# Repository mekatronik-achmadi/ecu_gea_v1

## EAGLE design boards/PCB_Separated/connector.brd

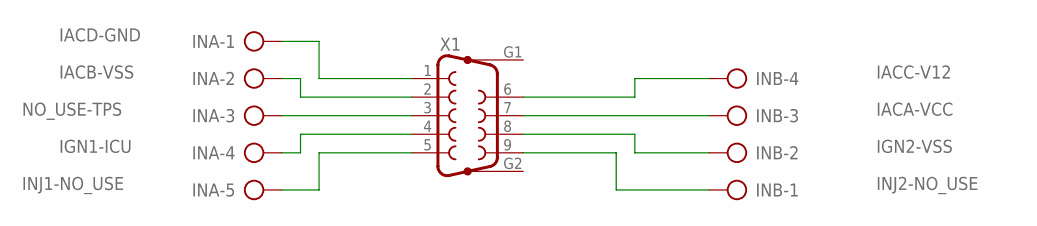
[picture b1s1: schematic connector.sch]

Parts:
INA: AK500/5
INB: AK500/4
X1: F09HP

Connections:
IACA-VCC: INB.3, X1.7
IACB-VSS: INA.2, X1.2
IACC-V12: INB.4, X1.6
IACD-GND: INA.1, X1.1
IGN1-ICU: INA.4, X1.4
IGN2-VSS: INB.2, X1.8
INJ1-NO_USE: INA.5, X1.5
INJ2-NO_USE: INB.1, X1.9
NO_USE-TPS: INA.3, X1.3

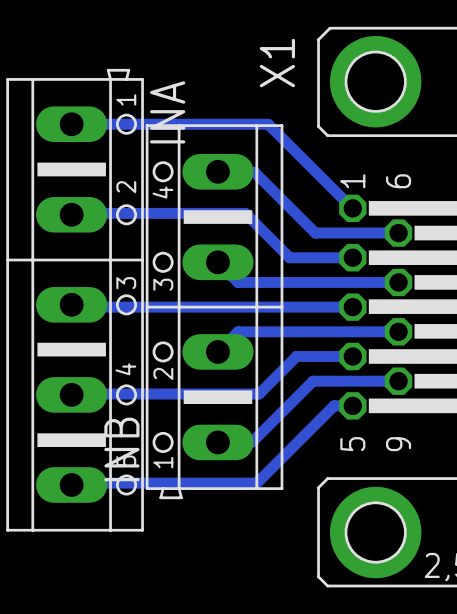
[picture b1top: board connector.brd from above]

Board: 2 copper layers, 3 parts (0 on the bottom side), 9 nets.

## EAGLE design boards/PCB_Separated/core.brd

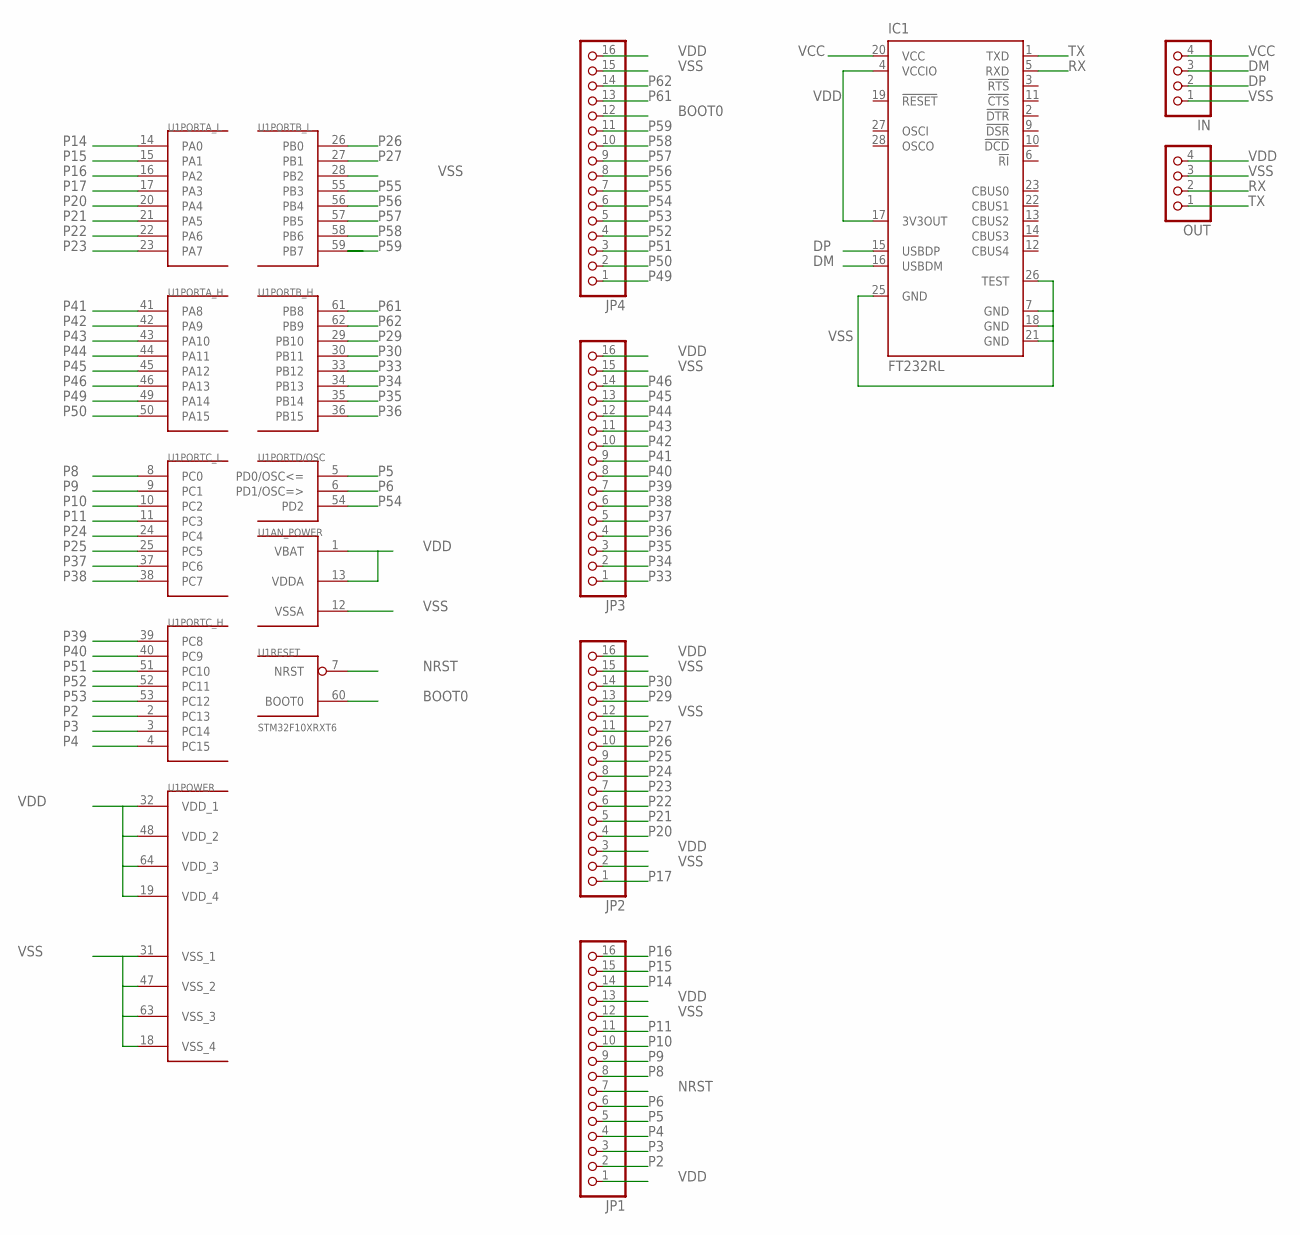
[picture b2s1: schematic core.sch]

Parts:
IC1: FT232RL; SSOP28
IN: PINHD-1X4; 1X04
JP1, JP2, JP3, JP4: PINHD-1X16; 1X16
OUT: PINHD-1X4; 1X04
U1: STM32F10XRXT6; TQFP64

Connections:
BOOT0: JP4.12, U1.60 (BOOT0)
DM: IC1.16 (USBDM), IN.3
DP: IC1.15 (USBDP), IN.2
NRST: JP1.7, U1.7 (NRST)
P2: JP1.2, U1.2 (PC13)
P3: JP1.3, U1.3 (PC14)
P4: JP1.4, U1.4 (PC15)
P5: JP1.5, U1.5 (PD0/OSC<=)
P6: JP1.6, U1.6 (PD1/OSC=>)
P8: JP1.8, U1.8 (PC0)
P9: JP1.9, U1.9 (PC1)
P10: JP1.10, U1.10 (PC2)
P11: JP1.11, U1.11 (PC3)
P14: JP1.14, U1.14 (PA0)
P15: JP1.15, U1.15 (PA1)
P16: JP1.16, U1.16 (PA2)
P17: JP2.1, U1.17 (PA3)
P20: JP2.4, U1.20 (PA4)
P21: JP2.5, U1.21 (PA5)
P22: JP2.6, U1.22 (PA6)
P23: JP2.7, U1.23 (PA7)
P24: JP2.8, U1.24 (PC4)
P25: JP2.9, U1.25 (PC5)
P26: JP2.10, U1.26 (PB0)
P27: JP2.11, U1.27 (PB1)
P29: JP2.13, U1.29 (PB10)
P30: JP2.14, U1.30 (PB11)
P33: JP3.1, U1.33 (PB12)
P34: JP3.2, U1.34 (PB13)
P35: JP3.3, U1.35 (PB14)
P36: JP3.4, U1.36 (PB15)
P37: JP3.5, U1.37 (PC6)
P38: JP3.6, U1.38 (PC7)
P39: JP3.7, U1.39 (PC8)
P40: JP3.8, U1.40 (PC9)
P41: JP3.9, U1.41 (PA8)
P42: JP3.10, U1.42 (PA9)
P43: JP3.11, U1.43 (PA10)
P44: JP3.12, U1.44 (PA11)
P45: JP3.13, U1.45 (PA12)
P46: JP3.14, U1.46 (PA13)
P49: JP4.1, U1.49 (PA14)
P50: JP4.2, U1.50 (PA15)
P51: JP4.3, U1.51 (PC10)
P52: JP4.4, U1.52 (PC11)
P53: JP4.5, U1.53 (PC12)
P54: JP4.6, U1.54 (PD2)
P55: JP4.7, U1.55 (PB3)
P56: JP4.8, U1.56 (PB4)
P57: JP4.9, U1.57 (PB5)
P58: JP4.10, U1.58 (PB6)
P59: JP4.11, U1.59 (PB7)
P61: JP4.13, U1.61 (PB8)
P62: JP4.14, U1.62 (PB9)
RX: IC1.5 (RXD), OUT.2
TX: IC1.1 (TXD), OUT.1
VCC: IC1.20 (VCC), IN.4
VDD: IC1.4 (VCCIO), IC1.17 (3V3OUT), JP1.1, JP1.13, JP2.3, JP2.16, JP3.16, JP4.16, OUT.4, U1.1 (VBAT), U1.13 (VDDA), U1.19 (VDD_4), U1.32 (VDD_1), U1.48 (VDD_2), U1.64 (VDD_3)
VSS: IC1.7 (GND), IC1.18 (GND), IC1.21 (GND), IC1.25 (GND), IC1.26 (TEST), IN.1, JP1.12, JP2.2, JP2.12, JP2.15, JP3.15, JP4.15, OUT.3, U1.12 (VSSA), U1.18 (VSS_4), U1.28 (PB2), U1.31 (VSS_1), U1.47 (VSS_2), U1.63 (VSS_3)

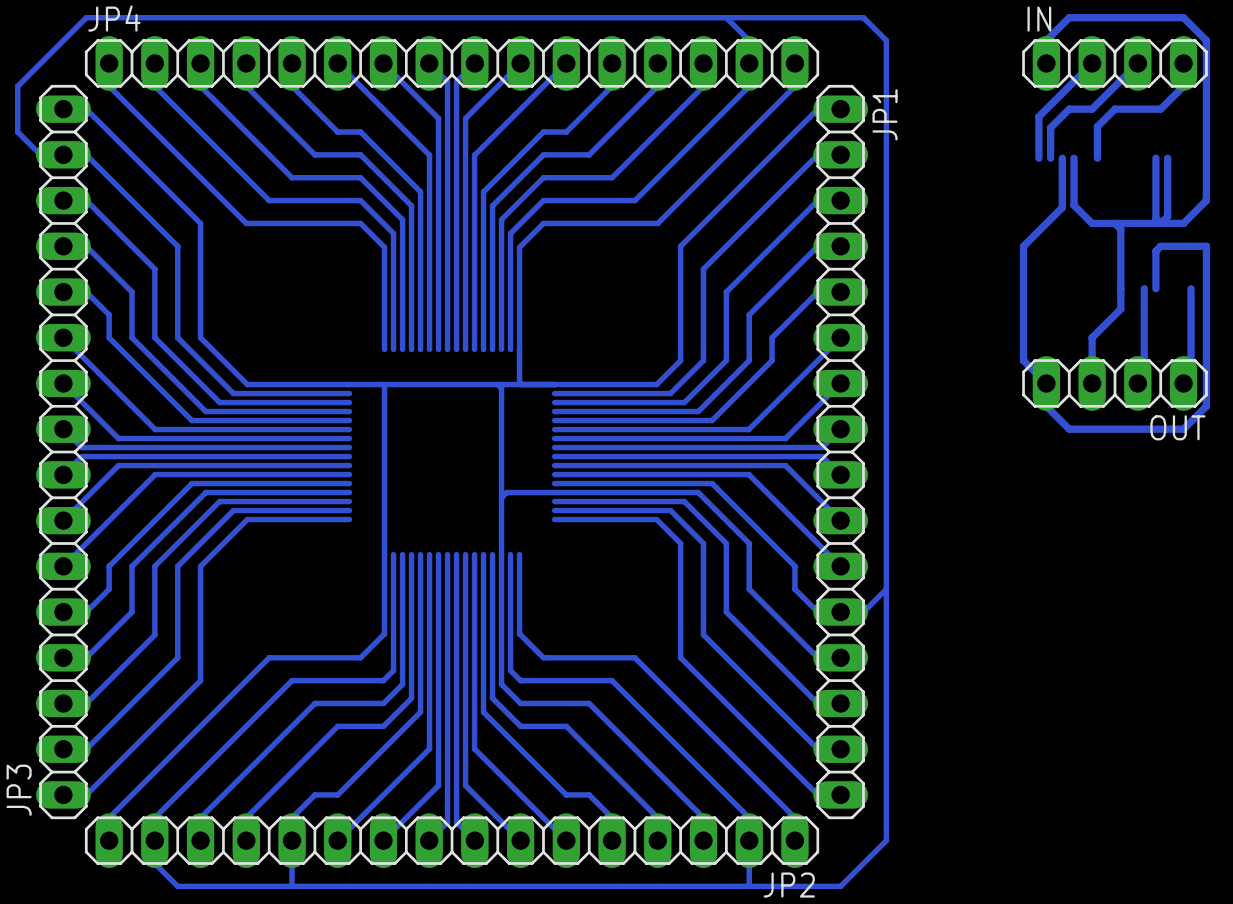
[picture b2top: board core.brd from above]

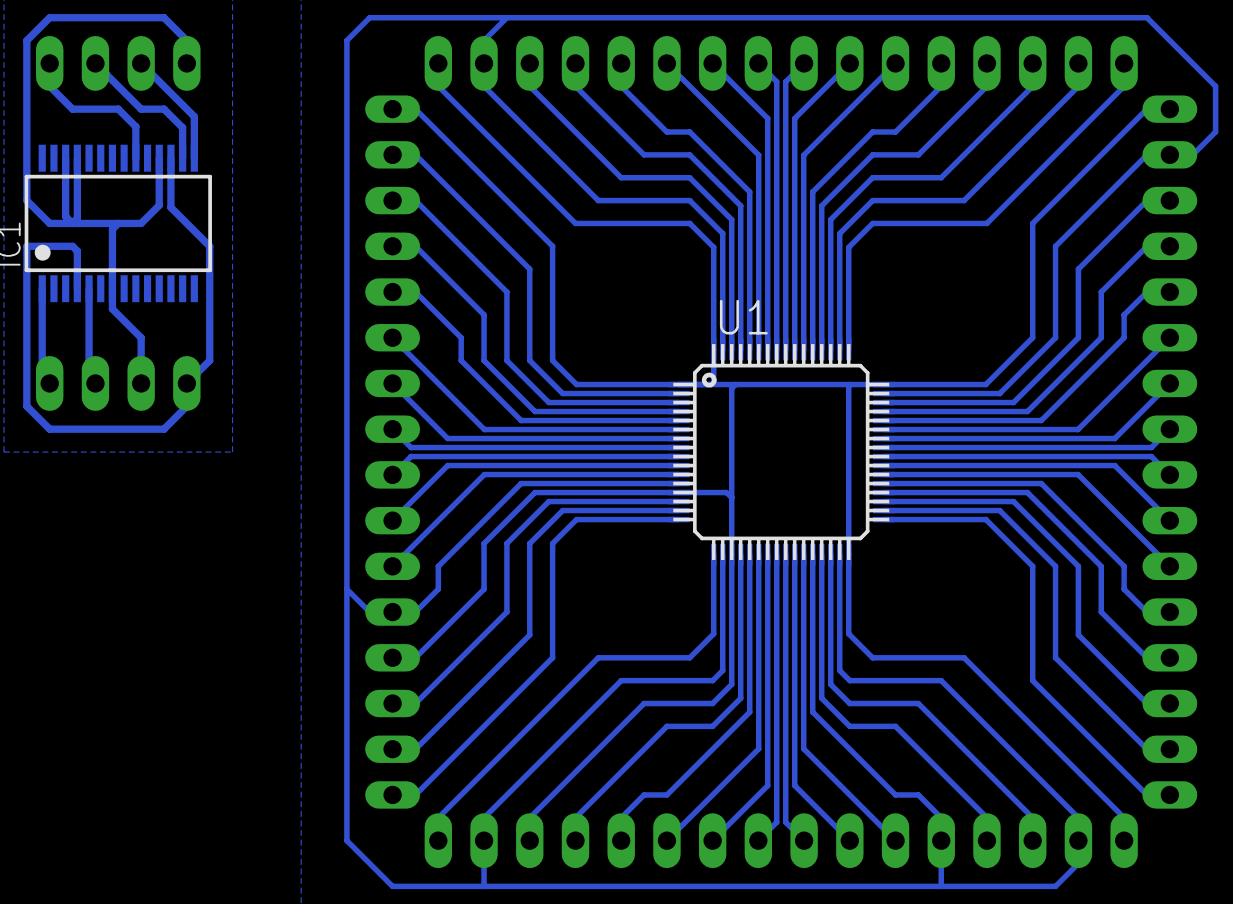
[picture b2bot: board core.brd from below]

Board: 2 copper layers, 8 parts (2 on the bottom side), 59 nets.

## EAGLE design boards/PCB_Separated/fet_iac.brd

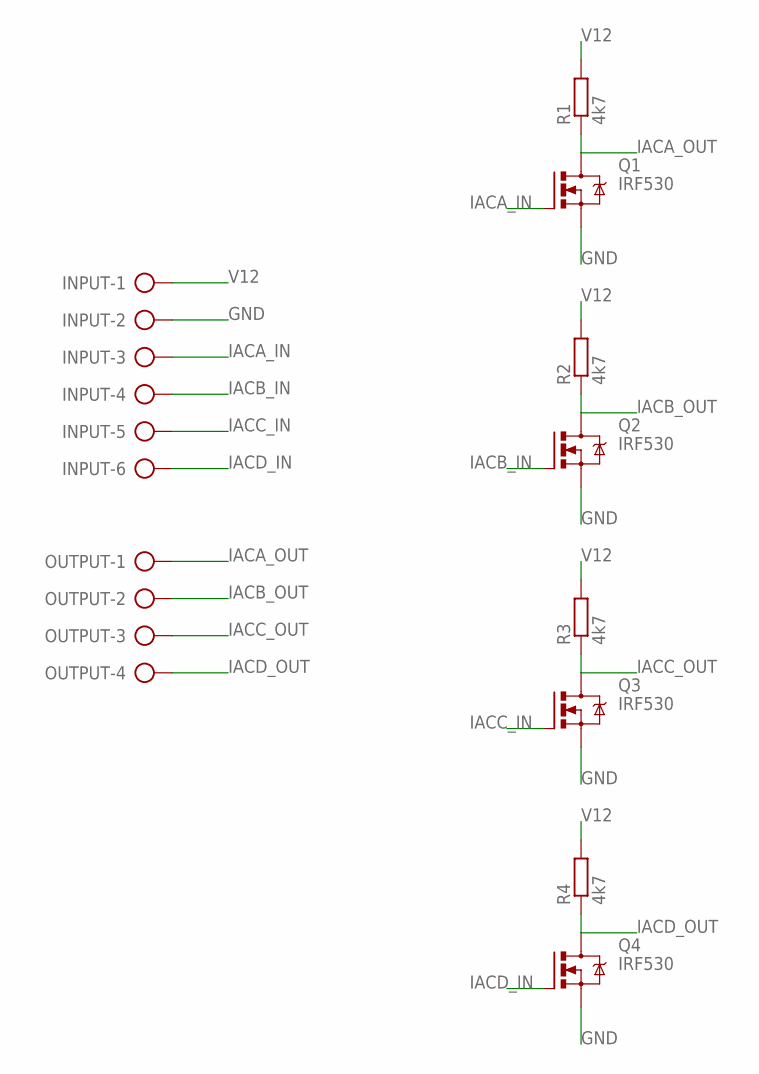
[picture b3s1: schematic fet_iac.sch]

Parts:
INPUT: AK500/6
OUTPUT: AK500/4
Q1, Q2, Q3, Q4: IRF530; TO220BV
R1, R2, R3, R4: 4k7; 0204/7

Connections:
GND: INPUT.2, Q1.S, Q2.S, Q3.S, Q4.S
IACA_IN: INPUT.3, Q1.G
IACA_OUT: OUTPUT.1, Q1.D, R1.1
IACB_IN: INPUT.4, Q2.G
IACB_OUT: OUTPUT.2, Q2.D, R2.1
IACC_IN: INPUT.5, Q3.G
IACC_OUT: OUTPUT.3, Q3.D, R3.1
IACD_IN: INPUT.6, Q4.G
IACD_OUT: OUTPUT.4, Q4.D, R4.1
V12: INPUT.1, R1.2, R2.2, R3.2, R4.2

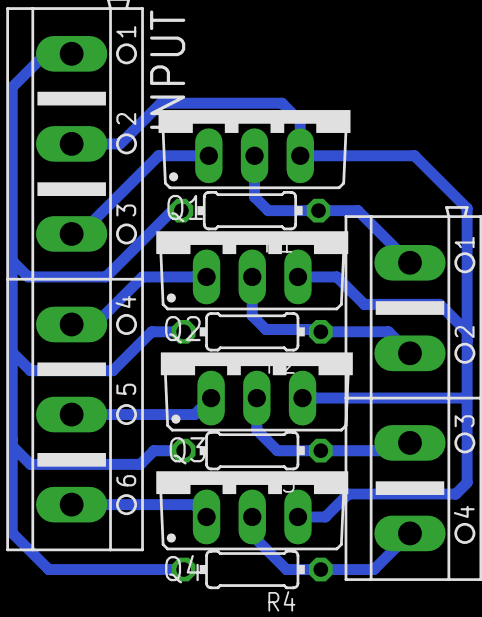
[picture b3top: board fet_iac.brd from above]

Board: 2 copper layers, 10 parts (0 on the bottom side), 10 nets.
